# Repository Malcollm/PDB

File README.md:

# WiscoHumanoids Power Distribution Board

This repository contains the power distribution board (PDB) for the WiscoHumanoids humanoid robot. The board takes the 48 V battery, precharges the main bus, and distributes power to four high-current actuator branches. It also generates regulated 24 V, 6 V and 3.3 V rails for compute, hand servos, and sensors/control electronics.

**Status: Rev 1 has been fabricated and assembled by JLCPCB.**

## Rev 1 at a Glance

| | |
|---|---|
| Board size | 178.6 mm × 242.3 mm |
| Layers | 6 (FR-4 TG155, 1.6 mm) |
| Copper | 2 oz outer, 1 oz inner |
| Input | 48 V battery, 70 A BF1 main fuse |
| Current rating | 70 A for a few minutes; actuators expected to draw about 10 A RMS, 21 A peak (see [Current Ratings](#current-ratings)) |
| Outputs | 4 × 48 V actuator branches (XT30), 2 × 24 V, 1 × 6 V, 1 × 3.3 V |
| Current sensing | 7 × ACS758LCB-100B Hall-effect sensors (±100 A) |
| Assembly | 207 SMT/THT placements per board by JLCPCB (69 BOM lines); fuses and fuse holders installed by hand |

## Board Renders

| Isometric | Top |
|---|---|
|  |  |

## Copper Layers

Each layer is shown with the board outline and silkscreen so parts can be located on it.

| L1 (top) | L2 |
|---|---|
|  |  |
| Components, signal routing, 48 V power pours, PGND | Solid PGND plane |

| L3 | L4 |
|---|---|
|  |  |
| 48 V power pours (paralleling L1), PGND, some signal routing | Solid PGND plane |

| L5 | L6 (bottom) |
|---|---|
|  |  |
| PGND, signal routing | Signal routing, PGND |

The full schematic is in [`images/schematic.pdf`](images/schematic.pdf).

## System Power Architecture

```text
Battery + (J3)
   |
   F1  70 A main fuse (BF1)
   |
   +-- RPRE1 precharge resistor ---+
   +-- Precharge contactor --------+   (off-board, J13 -> J14)
                                   |
                       48V_PRECH: 6 x 470 uF bulk (2.82 mF)
                                   |
                       U4  main current sensor
                                   |
                               48V_MAIN
   +-------------------------------+-------------------------------+
   |                               |                               |
   F2                         3.3 V buck (U3)            E-stop contactor (off-board,
   24 V buck (U2)                  |                     JESTOP1 -> JESTOP2)
   U5  24 V current sensor         J4  3.3 V out                   |
   |                                                           48V_ESTOP -- Brake chopper / regen dump
   J5  24 V -> Jetson                                              |         (dump resistor on J16/J17)
   J6  24 V -> USB-C PD controller                                 U8  actuator group current sensor
                                                                   |
                                                                48V_ACT
                     +--------------+--------------+--------------+--------------+
                     |              |              |              |              |
                     F7             F6             F5             F4             F3
                     U10            U9             U12            U11            6 V buck (U7)
                     J8  ACT1       J7  ACT2       J10 ACT3       J9  ACT4       J12  6 V -> hand servos
```

Compute and control (24 V, 3.3 V) is fed from `48V_MAIN`, ahead of the E-stop contactor. It stays powered when the E-stop opens, so the robot can still monitor, communicate and shut down safely. Everything that moves (the four actuator branches and the 6 V hand-servo rail) is fed from `48V_ACT`, after the E-stop contactor.

## Power Rails

| Rail | Generated by | Connector(s) | Purpose |
|---|---|---|---|
| 48 V | Battery, through F1 and precharge | J8, J7, J10, J9 (XT30) | Actuator branches ACT1–ACT4, each individually fused and current-sensed |
| 24 V | LM5148 synchronous buck controller (U2), 10 µH | J5, J6 (Phoenix MC 3.81 mm) | Jetson compute and USB-C PD controller |
| 6 V | LM5148 synchronous buck controller (U7), 4.7 µH | J12 (Phoenix MC 3.81 mm) | Servo motors in the robot hands (E-stop protected) |
| 3.3 V | LMR36015 buck regulator (U3), 18 µH | J4 (Phoenix MC 3.81 mm) | Sensors, current sensors, regen comparator, control logic |

## Current Ratings

| | Current |
|---|---|
| Board rating | 70 A for a few minutes (exact duration to be confirmed by a Rev 1 load test) |
| Main fuse (F1) | 70 A Littelfuse BF1, 142.5631.5702 (58 V, M5 bolt-down) |
| Expected actuator draw | About 10 A RMS walking at 1.0 m/s; peaks of about 21 A (100 ms) and 28 A (10 ms) |

These are design targets. Rev 1 has not been load or thermally tested yet.

**Why the rating is far above the expected load:** the board is deliberately oversized. Rev 1's power path was laid out before we had current numbers for the robot. Those came later, from a walking simulation of the actuators. It counts the motors only, with no regen, and has about ±25% uncertainty. The worst case was walking at 1.0 m/s: about 10 A RMS at the battery, with peaks of about 21 A over 100 ms and 28 A over 10 ms. We still want the board rated well above that, with room for roughly twice the actuator current for future expansion. That headroom covers the actuators only; the compute and servo rails draw current on top of it.

Each output also has a limit set by its parts:

| Output | Limit | Set by |
|---|---|---|
| Each actuator output (ACT1–ACT4) | 15 A continuous, 30 A for 1 minute | XT30 connector |
| 24 V rail | About 8 A (190 W) | 24 V buck inductor (8.7 A rated) and 8 A per output connector |
| 6 V rail | 8 A (48 W) | J12 connector |
| 3.3 V rail | 1.5 A | LMR36015 regulator |

## Signal Connectors

The PDB has three low-voltage signal connectors, all JST-GH (1.25 mm pitch). They use 3.3 V logic and are referenced to PGND. In the tables below, **In** and **Out** are from the PDB's point of view.

| Connector | Pins | Purpose |
|---|---|---|
| J11 | 8 | Current-sense outputs |
| J2 | 4 | E-stop control and feedback |
| J24 | 6 | Precharge board interface |

The contactor coil and E-stop button terminals (J20, J21, J22) run at battery voltage, not logic level. They are covered under [Precharge Circuit](#precharge-circuit) and [E-Stop and Actuator Disconnect](#e-stop-and-actuator-disconnect).

### J11: Current Sense Outputs (JST-GH 8-pin)

| Pin | Net | Dir | Function |
|---|---|---|---|
| 1 | `Act_rail_curr` | Out | Actuator group current |
| 2 | (unnamed) | Out | ACT1 current |
| 3 | (unnamed) | Out | ACT2 current |
| 4 | (unnamed) | Out | ACT3 current |
| 5 | (unnamed) | Out | ACT4 current |
| 6 | `Main_curr` | Out | Main battery current |
| 7 | `Com_cur` | Out | 24 V rail current |
| 8 | GND | | PGND |

To convert the readings to amps, see [Analog Conversions](#analog-conversions).

### J2: E-Stop Logic (JST-GH 4-pin)

| Pin | Net | Dir | Function |
|---|---|---|---|
| 1 | GND | | PGND |
| 2 | `ESTOP_FB` | Out | Low when the E-stop contactor coil is on |
| 3 | `ESTOP_EN2` | In | E-stop contactor enable 2 |
| 4 | `ESTOP_EN1` | In | E-stop contactor enable 1 |

The actuators are powered only when both enables are high and the E-stop button is closed. The enables are pulled down, so an unplugged connector keeps the actuators off.

### J24: Precharge Board Interface (JST-GH 6-pin)

| Pin | Net | Dir | Function |
|---|---|---|---|
| 1 | GND | | PGND |
| 2 | +3.3V | Out | 3.3 V supply for the precharge board |
| 3 | `PRECH_EN` | In | Closes the precharge contactor |
| 4 | `24V_EN_IN` | In | Turns on the 24 V rail |
| 5 | `PRECH_SENSE` | Out | Bus voltage ÷ 26.6 |
| 6 | `BATT_SENSE` | Out | Battery voltage ÷ 26.6 |

Both enables are active high and default to off. The precharge board compares the bus and battery voltages, then closes the contactor once the bus has charged. The 24 V rail stays off until it is enabled, which keeps the Jetson's load off the precharge resistor.

### Analog Conversions

To log the analog outputs, convert the voltage measured at the pin (`V`) as follows:

| Signal | Pins | Conversion | Range |
|---|---|---|---|
| Current sense | J11 pins 1–7 | `I (A) = (V − 1.65) / 0.0132` | ±100 A spans 0.33–2.97 V; 0 A reads 1.65 V |
| `PRECH_SENSE`, `BATT_SENSE` | J24 pins 5–6 | `Voltage (V) = V × 26.64` | 48 V reads 1.80 V; 3.3 V at the pin is 87.9 V |

- Positive current flows toward the load. Negative current is regen flowing back toward the battery.
- The current-sense outputs scale with the PDB's 3.3 V rail. If the logger's ADC uses a different reference, multiply 1.65 and 0.0132 by (measured 3.3 V rail ÷ 3.3).

## Major Board Features

### 48 V Actuator Distribution

The main power path distributes 48 V battery power to four actuator branches. Each branch has its own 20 A ATO blade fuse (F4–F7), current sensor and TVS diode, and leaves the board on an XT30 connector. Because this path carries the highest current on the board, the 48 V nets are poured on both L1 and L3, with short current paths and bolt-down M5 connections for the battery and contactors.

### Precharge Circuit

The main bus carries 2.82 mF of bulk capacitance, so connecting the battery directly would cause a large inrush current. The precharge resistor RPRE1 sits permanently across an off-board precharge contactor (J13/J14), so the bus charges slowly through RPRE1 when the battery is connected. An external controller watches the battery and bus voltages, then closes the contactor (through an MCP1402 gate driver and Q1) to bypass the resistor.

The precharge board connects on **J24** (pinout in [Signal Connectors](#j24-precharge-board-interface-jst-gh-6-pin)). The contactor coil connects to **J22**.

### E-Stop and Actuator Disconnect

An off-board E-stop contactor between JESTOP1 and JESTOP2 separates the actuator/servo group from the compute/control group. Its coil (**J20**) is powered through the normally-closed E-stop button (**J21**) and two series FETs (Q2/Q3), driven by MCP1402 gate drivers. The two enables and a feedback line are on **J2** (pinout in [Signal Connectors](#j2-e-stop-logic-jst-gh-4-pin)). Opening either the button or an enable drops the actuator group while compute stays up.

### Regen Protection (Brake Chopper)

When actuators decelerate they push energy back into the bus. If the battery can't take it (E-stop open, BMS charge FET open, or a full pack), the bus voltage rises. A TLV3011 comparator (U1) watches the actuator bus. When it crosses its trip point, a UCC27511 gate driver (U6) switches Q6/Q9 to dump the excess into an external 1 Ω, 200 W chassis-mount resistor on **J16/J17**. Pulling jumper **J18** (`BC_Disconnect`) disables the chopper.

### Current Sensing

Seven ACS758LCB-100B bidirectional Hall-effect sensors monitor:

| Sensor | Path |
|---|---|
| U4 | Main battery input (after precharge) |
| U8 | Actuator group, after the E-stop contactor |
| U10, U9, U12, U11 | Actuator branches ACT1–ACT4 |
| U5 | 24 V rail output |

Each output is RC-filtered and brought out on **J11** for the robot's controller (pinout in [J11](#j11-current-sense-outputs-jst-gh-8-pin), scaling in [Analog Conversions](#analog-conversions)). Current measurement is used for detecting abnormal loads, debugging actuator behavior, estimating power use, and measuring regen.

### Protection

- 70 A main fuse (F1, Littelfuse BF1 142.5631.5702, M5 bolt-down)
- 20 A ATO blade fuses on each actuator branch (F4–F7), a 10 A fuse on the 24 V compute buck input (F2) and a 5 A fuse on the 6 V servo buck input (F3)
- 0.5 A fuses on the contactor coil supplies (F8, F10)
- SMC TVS diodes on the fused 48 V input, each actuator branch, and the 24 V and 6 V outputs
- Varistor across the E-stop contactor coil; flyback diode on the precharge contactor coil
- Precharge / inrush-current limiting
- Brake-chopper regen dump
- Separation between actuator/servo power and compute/control power

### Test Points

TP1–TP16 and TP20 are Keystone 5015 test points on PGND, the E-stop, precharge and regen-dump control signals, and the converter bias rails. TP17–TP19 are bare probe pads on the switch nodes of the 24 V, 6 V and 3.3 V converters.

### Off-Board Parts (Rev 1)

Rev 1 has these parts mounted off the board, bolted to its M5 pads:

| Part | Connects to | Rev 2 plan |
|---|---|---|
| Precharge contactor | J13 / J14 (coil on J22) | Replace with power FETs on the board |
| E-stop contactor | JESTOP1 / JESTOP2 (coil on J20) | Replace with power FETs on the board |
| 1 Ω, 200 W chassis-mount dump resistor | J16 / J17 | Find a smaller solution |
| Dump resistor freewheel diode (DFB2) | Across the dump resistor: cathode to J16, anode to J17 | Move onto the board |

## Grounding

The board uses one power ground plus local analog grounds:

| Net | Purpose |
|---|---|
| PGND | High-current power ground and switching converter return. Continuous reference planes on L2 and L4; on L1, L3, L5 and L6 it is poured around signal routing |
| AGND, AGND1–AGND10 | Local analog grounds for each buck converter's feedback network, each current sensor, and the regen comparator |

Each local AGND joins PGND at one point through a net tie (NT1–NT11). This keeps large return currents out of the feedback and measurement references.

## Simulations

LTspice simulations live in [`LTspice Simulations/`](LTspice%20Simulations/). Each folder has a `.lib` of behavioral models and the matching `.asy` symbols the schematics use.

| Simulation | Purpose |
|---|---|
| `precharge/precharge_resistor_sweep.asc` | Sweeps the precharge resistor value (the board uses 100 Ω) to compare bus charge time against resistor and main-fuse stress |
| `precharge/precharge_load_sweep.asc` | With the board's 100 Ω resistor, sweeps the load drawn during precharge to check the bus still reaches full voltage before the contactor closes |
| `regen/regen_earlier_design.asc` | An earlier version of the regen dump circuit, kept for reference. It is expected to fail its checks; the sim below shows the fixes |
| `regen/regen_current_sweep.asc` | The regen dump circuit with the fixes (freewheel diode, local ceramic, sense filter, gate pulldown), the board's resistor values and TVS diodes, and the 1 Ω dump resistor. Sweeps regen current from 10 to 50 A, held for 10 ms; 28 A is the worst 10 ms battery peak from the walking simulation. Checks the actuators stay under their 55 V maximum, the dump FET under 80 V, and the TVS diodes don't conduct |

Results are written to the SPICE output log as `.meas` values, including pass/fail checks.

## Repository Layout

| Path | Contents |
|---|---|
| `Main_PDB.kicad_pro` / `.kicad_sch` / `.kicad_pcb` | KiCad 10 project, schematic and board |
| `Main_PDB.kicad_dru` | Custom design rules (JLCPCB 6-layer, 2 oz outer copper limits, net-tie exceptions) |
| `Footprints.pretty/`, `Symbols/`, `3d Models/` | Project libraries and 3D models |
| `production/` | Rev 1 manufacturing outputs: gerbers (`PDB_PCB.zip`), BOM, pick-and-place, IPC netlist |
| `images/` | Board renders, layer SVGs and schematic PDF, regenerated from the design files (see [`images/regenerate-images.md`](images/regenerate-images.md)) |
| `LTspice Simulations/` | Precharge and regen protection simulations |

The images are rebuilt by a pre-commit hook whenever the board or schematic changes. Enable it once per clone with `git config core.hooksPath images/hooks`.

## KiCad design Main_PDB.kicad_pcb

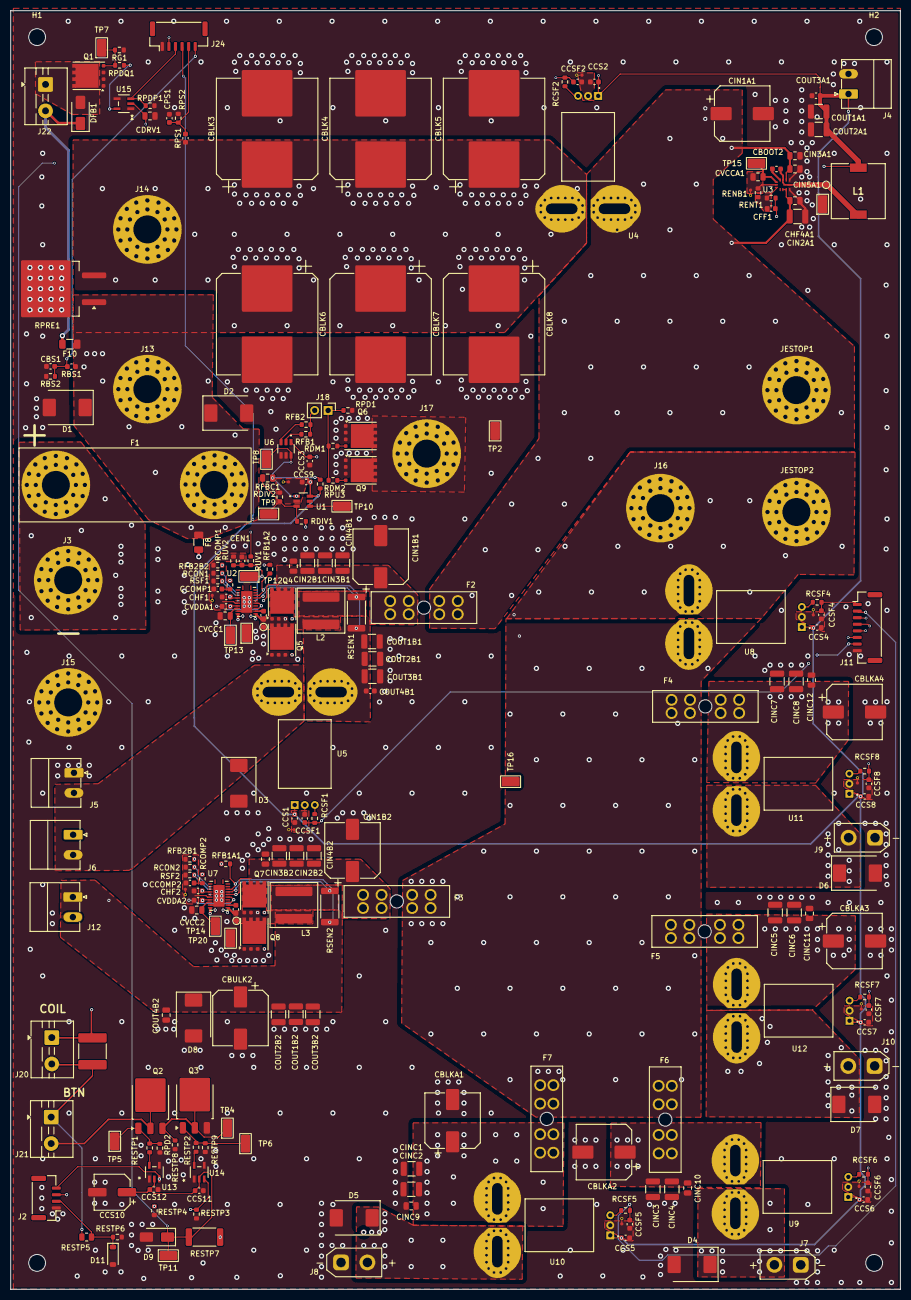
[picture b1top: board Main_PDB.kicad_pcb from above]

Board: 6 copper layers, 168.6 x 242.3 mm, 241 parts (0 on the bottom side), 105 nets.

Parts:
CBLK3, CBLK4, CBLK5, CBLK6, CBLK7, CBLK8: 470uF; CP_Elec_18x22
CBLKA1, CBLKA2: 100uF; CP_Elec_10x10
CBLKA3, CBLKA4: 47uF; CP_Elec_10x10
CBOOT1, CBOOT2, CBOOT3: 100nF; C_0603_1608Metric
CBS1: 100nF; C_0603_1608Metric
CBULK2: 100uF; CP_Elec_10x10
CCOMP1: 2nF; C_0603_1608Metric
CCOMP2: 2.7nF; C_0603_1608Metric
CCS1, CCS2, CCS3, CCS4, CCS5, CCS6, CCS7, CCS8, CCS9, CCS11, CCS12: 100nF; C_0603_1608Metric
CCS10: 100uF; CP_Elec_6.3x5.4
CCSF1, CCSF2, CCSF4, CCSF5, CCSF6, CCSF7, CCSF8: 10nF; C_0603_1608Metric
CDRV1: 1uF; C_0805_2012Metric
CEN1: 1nF; C_0603_1608Metric
CFF1: 22pF; C_0603_1608Metric
CHF1, CHF2: 22pF; C_0603_1608Metric
CHF4A1: 220nF; C_0805_2012Metric
CIN1A1, CIN1B1: 47uF; CP_Elec_10x10
CIN1B2: 100uF; CP_Elec_10x10
CIN2A1, CIN2B1, CIN2B2, CIN3B1, CIN3B2, CIN4B1, CIN4B2: 4.7uF; C_1210_3225Metric
CIN3A1: 220nF; C_0805_2012Metric
CIN5A1, CIN5B1, CIN5B2: 100nF; C_0805_2012Metric
CINC1, CINC2, CINC3, CINC4, CINC5, CINC6, CINC7, CINC8: 4.7uF; C_1210_3225Metric
CINC9, CINC10, CINC11, CINC12: 100nF; C_0805_2012Metric
COUT1A1, COUT2A1: 47uF; C_1210_3225Metric
COUT1B1, COUT1B2, COUT2B1, COUT2B2, COUT3B1, COUT3B2: 22uF; C_1210_3225Metric
COUT3A1, COUT4B1: 100nF; C_0603_1608Metric
COUT4B2: 100nF; C_0805_2012Metric
CPS1: 100nF; C_0603_1608Metric
CVCC1, CVCC2: 2.2uF; C_0805_2012Metric
CVCCA1: 1uF; C_0805_2012Metric
CVDDA1, CVDDA2: 100nF; C_0603_1608Metric
D1, D2, D4, D5, D6, D7: SMCJ58A; D_SMC
D3: SMCJ26A; D_SMC
D8: SMCJ6.5A; D_SMC
D9: SMAZ12-13-F; D_SMA
D11: MMSZ5226BT1G; D_SOD-123
DFB1: S1M-13-F; D_SMA
F1: 70A; FUSE_BF1_M5
F2, F3, F4, F5, F6, F7: 178.6165.0002; LITTELFUSE_178.6165.0002
F8, F10: 0.5A; Fuse_1206_3216Metric
H1, H2, H3, H4: MountingHole_3.2mm_M3
J2: E-stop Ctrl; JST_GH_BM04B-GHS-TBT_1x04-1MP_P1.25mm_Vertical
J3: Conn_Batt_PWR; MountingHole_5.3mm_M5_Pad_Via_HP
J4: 3.3V Out; PhoenixContact_MC_1,5_2-G-3.81_1x02_P3.81mm_Horizontal
J5: 24V Out -> Jetson; PhoenixContact_MC_1,5_2-G-3.81_1x02_P3.81mm_Horizontal
J6: 24V Out -> USB-C-PD controller; PhoenixContact_MC_1,5_2-G-3.81_1x02_P3.81mm_Horizontal
J7: ACT2 Out; AMASS_XT30UPB-F_1x02_P5.0mm_Vertical
J8: ACT1 Out; AMASS_XT30UPB-F_1x02_P5.0mm_Vertical
J9: ACT4 Out; AMASS_XT30UPB-F_1x02_P5.0mm_Vertical
J10: ACT3 Out; AMASS_XT30UPB-F_1x02_P5.0mm_Vertical
J11: Current Sense Out; JST_GH_BM08B-GHS-TBT_1x08-1MP_P1.25mm_Vertical
J12: 6V Out; PhoenixContact_MC_1,5_2-G-3.81_1x02_P3.81mm_Horizontal
J13: PRECIN; MountingHole_5.3mm_M5_Pad_Via_HP
J14: PRECOUT; MountingHole_5.3mm_M5_Pad_Via_HP
J15: Conn_Batt_GND; MountingHole_5.3mm_M5_Pad_Via_HP
J16: Dump_Resistor_In; MountingHole_5.3mm_M5_Pad_Via_HP
J17: Dump_Resistor_Out; MountingHole_5.3mm_M5_Pad_Via_HP
J18: BC_Disconnect; PinHeader_1x02_P2.54mm_Vertical
J20: ESTOP Contactor Coil Control; TerminalBlock_MaiXu_MX126-5.0-02P_1x02_P5.00mm
J21: ESTOP Button (Normally Closed); TerminalBlock_MaiXu_MX126-5.0-02P_1x02_P5.00mm
J22: Precharge Contactor Coil Control; TerminalBlock_MaiXu_MX126-5.0-02P_1x02_P5.00mm
J24: Precharge Ctrl In; JST_GH_BM06B-GHS-TBT_1x06-1MP_P1.25mm_Vertical
JESTOP1: ESTOP_IN; MountingHole_5.3mm_M5_Pad_Via_HP
JESTOP2: ESTOP_OUT; MountingHole_5.3mm_M5_Pad_Via_HP
L1: 18uH; L_Sumida_CDRH104R
L2: 10uH; L_Coilank_AAPS0880
L3: 4.7uH; L_Coilcraft_XAL8080-XXX
NT1, NT2, NT3, NT4, NT5, NT6, NT7, NT8, NT9, NT10, NT11: NetTie_2; NetTie_AGND_PGND_VIA
Q1, Q5, Q6, Q8, Q9: BSC070N10LS5ATMA1; VSONP-8-1EP_5x6_P1.27mm
Q2, Q3: IRFR220TRPBF; TO-252-3_TabPin2
Q4, Q7: BSC146N10LS5; VSONP-8-1EP_5x6_P1.27mm
RBS1: 100k; C_0603_1608Metric
RBS2: 3.9k; R_0603_1608Metric
RCOMP1: 19.1k; R_0603_1608Metric
RCOMP2: 12.1k; R_0603_1608Metric
RCON1, RCON2: 41.2k; R_0603_1608Metric
RCSF1, RCSF2, RCSF4, RCSF5, RCSF6, RCSF7, RCSF8: 1k; R_0603_1608Metric
RDIV1: 1M; R_0603_1608Metric
RDIV2: 24k; R_0603_1608Metric
RDM1, RDM2: 2.2R; R_0603_1608Metric
RENB1: 43.2k; R_0603_1608Metric
RENT1: 100k; R_0603_1608Metric
RESTP1, RESTP2: 100R; R_0603_1608Metric
RESTP3, RESTP4: 2.2k; R_0603_1608Metric
RESTP5: 100k; R_0805_2012Metric
RESTP6: 7.5k; R_0603_1608Metric
RESTP7: 4.7k; R_2512_6332Metric
RESTP8, RESTP9: 100k; R_0603_1608Metric
RFB1, RFB2: 4.7R; R_0603_1608Metric
RFB1A1: 64.9k; R_0603_1608Metric
RFB1A2: 291k; R_0603_1608Metric
RFB2B1, RFB2B2: 10k; R_0603_1608Metric
RFBC1: 1.6M; C_0805_2012Metric
RG1: 100R; R_0603_1608Metric
RPD1, RPD2: 100k; R_0603_1608Metric
RPDP1: 100k; R_0603_1608Metric
RPDQ1: 100k; R_0603_1608Metric
RPRE1: 100; TO-263-2_Resistor
RPS1: 100k; C_0603_1608Metric
RPS2: 3.9k; R_0603_1608Metric
RPU3: 10k; R_0603_1608Metric
RSEN1, RSEN2: 0.004R; R_2512_6332Metric
RSF1, RSF2: 47k; R_0603_1608Metric
RUV1, RUV2: 100k; R_0603_1608Metric
RV1: RL2220A820K-452A; C_2220_5750Metric
TP1, TP2, TP3, TP4, TP5, TP6, TP7, TP8, TP9, TP10, TP11, TP12, TP13, TP14, TP15, TP16: Keystone 5015; TestPoint_Keystone_5015_Micro_Mini
TP17, TP18, TP19: SW probe pad; TestPoint_Pad_D1.0mm
TP20: PGND probe pad; TestPoint_Keystone_5015_Micro_Mini
U1: TLV3011AIDBVT; SOT95P280X145-6N
U2, U7: LM5148RGYR; QFN50P550X350X100-25N
U3: LMR36015ARNXR; RNX0012B
U4, U5, U8, U9, U10, U11, U12: ACS758LCB-100B-PFF-T; XDCR_ACS758LCB-100B-PFF-T
U6: UCC27511DBVR; SOT95P280X145-6N
U13, U14, U15: MCP1402T-E/OT; SOT-23-5_MC_MCH

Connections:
+3.3V: CCS1.1, CCS2.2, CCS4.2, CCS5.1, CCS6.1, CCS7.1, CCS8.1, CCS9.1, CFF1.1, COUT1A1.1, COUT2A1.1, COUT3A1.1, J4.1, J24.2, L1.2, RENT1.1, RPU3.2, U1.6 (V+), U4.1 (VCC), U5.1 (VCC), U8.1 (VCC), U9.1 (VCC), U10.1 (VCC), U11.1 (VCC), U12.1 (VCC)
+6V: CBULK2.1, CCS3.1, COUT1B2.1, COUT2B2.1, COUT3B2.1, COUT4B2.1, D8.1 (K), J12.1, RFB1A1.2, RSEN2.2, U6.1 (VDD), U7.21 (VOUT)
+6V_IND: L3.2, RSEN2.1, U7.20 (ISNS+)
+24V: D3.1 (K), J5.2, J6.2, U5.5 (IP-), U5.5_1 (IP-), U5.5_2 (IP-), U5.5_3 (IP-), U5.5_4 (IP-), U5.5_5 (IP-), U5.5_6 (IP-), U5.5_7 (IP-), U5.5_8 (IP-), U5.5_9 (IP-), U5.5_10 (IP-), U5.5_11 (IP-), U5.5_12 (IP-), U5.5_13 (IP-), U5.5_14 (IP-), U5.5_15 (IP-), U5.5_16 (IP-)
+48V_BATT: F1.1, J3.1 (Pin_1_1)
/3V3_SW: CBOOT2.2, L1.1, TP19.1 (1_1), U3.3 (NC), U3.12 (SW)
/3V3_VCC: CVCCA1.2, TP15.1 (1_1), U3.5 (VCC)
/6V_FUSE: CIN1B2.1, CIN2B2.2, CIN3B2.2, CIN4B2.2, CIN5B2.2, F3.2_1, F3.2_2, F3.2_3, F3.2_4, Q7.3 (D), U7.12 (VIN), U7.19 (EN)
/6V_NMOS: CBOOT3.1, L3.1, Q7.1 (S), Q8.3 (D), TP18.1 (1_1), U7.14 (SW)
/6V_VCC: CVCC2.1, TP14.1 (1_1), U7.9 (VCC)
/12V_BIAS: CCS10.1, CCS11.2, CCS12.2, CDRV1.1, D9.1 (K), RESTP7.2, TP11.1 (1_1), U13.2 (VDD), U14.2 (VDD), U15.2 (VDD)
/24V_EN: CEN1.1, RUV1.2, RUV2.1, TP12.1 (1_1), U2.19 (EN)
/24V_EN_IN: J24.4, RUV1.1
/24V_FUSE: CIN1B1.1, CIN2B1.2, CIN3B1.2, CIN4B1.2, CIN5B1.2, F2.2_1, F2.2_2, F2.2_3, F2.2_4, Q4.3 (D), U2.12 (VIN)
/24V_IND: L2.2, RSEN1.1, U2.20 (ISNS+)
/24V_NMOS: CBOOT1.2, L2.1, Q4.1 (S), Q5.3 (D), TP17.1 (1_1), U2.14 (SW)
/24V_SEN: COUT1B1.1, COUT2B1.1, COUT3B1.1, COUT4B1.1, RFB1A2.2, RSEN1.2, U2.21 (VOUT), U5.4 (IP+), U5.4_1 (IP+), U5.4_2 (IP+), U5.4_3 (IP+), U5.4_4 (IP+), U5.4_5 (IP+), U5.4_6 (IP+), U5.4_7 (IP+), U5.4_8 (IP+), U5.4_9 (IP+), U5.4_10 (IP+), U5.4_11 (IP+), U5.4_12 (IP+), U5.4_13 (IP+), U5.4_14 (IP+), U5.4_15 (IP+), U5.4_16 (IP+)
/24V_VCC: CVCC1.1, TP13.1 (1_1), U2.9 (VCC)
/48V_ACT: F3.1_1, F3.1_2, F3.1_3, F3.1_4, F4.1_1, F4.1_2, F4.1_3, F4.1_4, F5.1_1, F5.1_2, F5.1_3, F5.1_4, F6.1_1, F6.1_2, F6.1_3, F6.1_4, F7.1_1, F7.1_2, F7.1_3, F7.1_4, U8.5 (IP-), U8.5_1 (IP-), U8.5_2 (IP-), U8.5_3 (IP-), U8.5_4 (IP-), U8.5_5 (IP-), U8.5_6 (IP-), U8.5_7 (IP-), U8.5_8 (IP-), U8.5_9 (IP-), U8.5_10 (IP-), U8.5_11 (IP-), U8.5_12 (IP-), U8.5_13 (IP-), U8.5_14 (IP-), U8.5_15 (IP-), U8.5_16 (IP-)
/48V_ACT1: D5.1 (K), J8.2, U10.5 (IP-), U10.5_1 (IP-), U10.5_2 (IP-), U10.5_3 (IP-), U10.5_4 (IP-), U10.5_5 (IP-), U10.5_6 (IP-), U10.5_7 (IP-), U10.5_8 (IP-), U10.5_9 (IP-), U10.5_10 (IP-), U10.5_11 (IP-), U10.5_12 (IP-), U10.5_13 (IP-), U10.5_14 (IP-), U10.5_15 (IP-), U10.5_16 (IP-)
/48V_ACT1_FUSE: CBLKA1.1, CINC1.2, CINC2.2, CINC9.1, F7.2_1, F7.2_2, F7.2_3, F7.2_4, U10.4 (IP+), U10.4_1 (IP+), U10.4_2 (IP+), U10.4_3 (IP+), U10.4_4 (IP+), U10.4_5 (IP+), U10.4_6 (IP+), U10.4_7 (IP+), U10.4_8 (IP+), U10.4_9 (IP+), U10.4_10 (IP+), U10.4_11 (IP+), U10.4_12 (IP+), U10.4_13 (IP+), U10.4_14 (IP+), U10.4_15 (IP+), U10.4_16 (IP+)
/48V_ACT2: D4.1 (K), J7.2, U9.5 (IP-), U9.5_1 (IP-), U9.5_2 (IP-), U9.5_3 (IP-), U9.5_4 (IP-), U9.5_5 (IP-), U9.5_6 (IP-), U9.5_7 (IP-), U9.5_8 (IP-), U9.5_9 (IP-), U9.5_10 (IP-), U9.5_11 (IP-), U9.5_12 (IP-), U9.5_13 (IP-), U9.5_14 (IP-), U9.5_15 (IP-), U9.5_16 (IP-)
/48V_ACT2_FUSE: CBLKA2.1, CINC3.2, CINC4.2, CINC10.1, F6.2_1, F6.2_2, F6.2_3, F6.2_4, U9.4 (IP+), U9.4_1 (IP+), U9.4_2 (IP+), U9.4_3 (IP+), U9.4_4 (IP+), U9.4_5 (IP+), U9.4_6 (IP+), U9.4_7 (IP+), U9.4_8 (IP+), U9.4_9 (IP+), U9.4_10 (IP+), U9.4_11 (IP+), U9.4_12 (IP+), U9.4_13 (IP+), U9.4_14 (IP+), U9.4_15 (IP+), U9.4_16 (IP+)
/48V_ACT3: D7.1 (K), J10.2, U12.5 (IP-), U12.5_1 (IP-), U12.5_2 (IP-), U12.5_3 (IP-), U12.5_4 (IP-), U12.5_5 (IP-), U12.5_6 (IP-), U12.5_7 (IP-), U12.5_8 (IP-), U12.5_9 (IP-), U12.5_10 (IP-), U12.5_11 (IP-), U12.5_12 (IP-), U12.5_13 (IP-), U12.5_14 (IP-), U12.5_15 (IP-), U12.5_16 (IP-)
/48V_ACT3_FUSE: CBLKA3.1, CINC5.2, CINC6.2, CINC11.1, F5.2_1, F5.2_2, F5.2_3, F5.2_4, U12.4 (IP+), U12.4_1 (IP+), U12.4_2 (IP+), U12.4_3 (IP+), U12.4_4 (IP+), U12.4_5 (IP+), U12.4_6 (IP+), U12.4_7 (IP+), U12.4_8 (IP+), U12.4_9 (IP+), U12.4_10 (IP+), U12.4_11 (IP+), U12.4_12 (IP+), U12.4_13 (IP+), U12.4_14 (IP+), U12.4_15 (IP+), U12.4_16 (IP+)
/48V_ACT4: D6.1 (K), J9.2, U11.5 (IP-), U11.5_1 (IP-), U11.5_2 (IP-), U11.5_3 (IP-), U11.5_4 (IP-), U11.5_5 (IP-), U11.5_6 (IP-), U11.5_7 (IP-), U11.5_8 (IP-), U11.5_9 (IP-), U11.5_10 (IP-), U11.5_11 (IP-), U11.5_12 (IP-), U11.5_13 (IP-), U11.5_14 (IP-), U11.5_15 (IP-), U11.5_16 (IP-)
/48V_ACT4_FUSE: CBLKA4.1, CINC7.2, CINC8.2, CINC12.1, F4.2_1, F4.2_2, F4.2_3, F4.2_4, U11.4 (IP+), U11.4_1 (IP+), U11.4_2 (IP+), U11.4_3 (IP+), U11.4_4 (IP+), U11.4_5 (IP+), U11.4_6 (IP+), U11.4_7 (IP+), U11.4_8 (IP+), U11.4_9 (IP+), U11.4_10 (IP+), U11.4_11 (IP+), U11.4_12 (IP+), U11.4_13 (IP+), U11.4_14 (IP+), U11.4_15 (IP+), U11.4_16 (IP+)
/48V_ESTOP: J16.1 (Pin_1_1), JESTOP2.1 (Pin_1_1), RDIV1.1, U8.4 (IP+), U8.4_1 (IP+), U8.4_2 (IP+), U8.4_3 (IP+), U8.4_4 (IP+), U8.4_5 (IP+), U8.4_6 (IP+), U8.4_7 (IP+), U8.4_8 (IP+), U8.4_9 (IP+), U8.4_10 (IP+), U8.4_11 (IP+), U8.4_12 (IP+), U8.4_13 (IP+), U8.4_14 (IP+), U8.4_15 (IP+), U8.4_16 (IP+)
/48V_FUSE: D1.1 (K), D2.1 (K), F1.2, F8.1, F10.1, J13.1 (Pin_1_1), RBS1.1, RPRE1.1
/48V_MAIN: CHF4A1.1, CIN1A1.1, CIN2A1.1, CIN3A1.1, CIN5A1.1, F2.1_1, F2.1_2, F2.1_3, F2.1_4, JESTOP1.1 (Pin_1_1), U3.2 (VIN), U3.9 (EN), U3.10 (VIN), U4.5 (IP-), U4.5_1 (IP-), U4.5_2 (IP-), U4.5_3 (IP-), U4.5_4 (IP-), U4.5_5 (IP-), U4.5_6 (IP-), U4.5_7 (IP-), U4.5_8 (IP-), U4.5_9 (IP-), U4.5_10 (IP-), U4.5_11 (IP-), U4.5_12 (IP-), U4.5_13 (IP-), U4.5_14 (IP-), U4.5_15 (IP-), U4.5_16 (IP-)
/48V_PRECH: CBLK3.1, CBLK4.1, CBLK5.1, CBLK6.1, CBLK7.1, CBLK8.1, J14.1 (Pin_1_1), RPRE1.2, RPS1.1, U4.4 (IP+), U4.4_1 (IP+), U4.4_2 (IP+), U4.4_3 (IP+), U4.4_4 (IP+), U4.4_5 (IP+), U4.4_6 (IP+), U4.4_7 (IP+), U4.4_8 (IP+), U4.4_9 (IP+), U4.4_10 (IP+), U4.4_11 (IP+), U4.4_12 (IP+), U4.4_13 (IP+), U4.4_14 (IP+), U4.4_15 (IP+), U4.4_16 (IP+)
/Act_rail_curr: CCSF4.2, J11.1, RCSF4.2
/BATT_SENSE: CBS1.1, J24.6, RBS1.2, RBS2.1
/Com_cur: CCSF1.2, J11.7, RCSF1.2
/DUMP_REF: TP10.1 (1_1), U1.4 (IN-), U1.5 (REF)
/DUMP_SENSE: RDIV1.2, RDIV2.1, RFBC1.2, TP9.1 (1_1), U1.3 (IN+)
/DUMP_TRIG: RFBC1.1, RPU3.1, TP8.1 (1_1), U1.1 (OUT), U6.6 (IN+)
/D_R_OUT: J17.1 (Pin_1_1), Q6.3 (D), Q9.3 (D)
/ESTOP_EN1: J2.4, RESTP4.2, U13.3 (IN)
/ESTOP_EN2: J2.3, RESTP3.1, U14.3 (IN)
/ESTOP_FB: D11.1 (K), J2.2, RESTP5.2, RESTP6.1
/ESTOP_FET_MID: Q2.3 (S), Q3.2 (D), RPD2.2, TP4.1 (1_1)
/ESTOP_G1: Q2.1 (G), RESTP1.1, RESTP8.1, TP5.1 (1_1)
/ESTOP_G2: Q3.1 (G), RESTP2.1, RESTP9.2, TP6.1 (1_1)
/Main_curr: CCSF2.2, J11.6, RCSF2.2
/PRECH_EN: J24.3, RPDP1.1, U15.3 (IN)
/PRECH_GATE: Q1.2 (G), RG1.1, RPDQ1.1, TP7.1 (1_1)
/PRECH_SENSE: CPS1.1, J24.5, RPS1.2, RPS2.1
AGND: CCS2.1, CCSF2.1, NT10.1, U4.2 (GND)
AGND1: CCS9.2, NT1.1, RDIV2.2, U1.2 (V-)
AGND2: CCOMP1.2, CEN1.2, CHF1.2, CVDDA1.1, NT2.1, RCON1.1, RFB2B2.1, RSF1.1, RUV2.2, U2.7 (AGND), U2.16 (VCCX), U2.18 (PFM/SYNC)
AGND3: CCOMP2.2, CHF2.2, CVDDA2.1, NT3.1, RCON2.1, RFB2B1.1, RSF2.1, U7.7 (AGND), U7.16 (VCCX), U7.18 (PFM/SYNC)
AGND4: CCS1.2, CCSF1.1, NT4.1, U5.2 (GND)
AGND5: CVCCA1.1, NT5.1, RENB1.2, U3.6 (AGND)
AGND6: CCS4.1, CCSF4.1, NT6.1, U8.2 (GND)
AGND7: CCS5.2, CCSF5.1, NT7.1, U10.2 (GND)
AGND8: CCS6.2, CCSF6.1, NT8.1, U9.2 (GND)
AGND9: CCS7.2, CCSF7.1, NT9.1, U12.2 (GND)
AGND10: CCS8.2, CCSF8.1, NT11.1, U11.2 (GND)
unnamed: CCOMP1.1, RCOMP1.2
unnamed: CCOMP2.1, RCOMP2.2
unnamed: DFB1.2 (A), J22.1, Q1.3 (D)
unnamed: DFB1.1 (K), F10.2, J22.2
unnamed: CCSF5.2, J11.2, RCSF5.2
unnamed: CCSF6.2, J11.3, RCSF6.2
unnamed: CCSF7.2, J11.4, RCSF7.2
unnamed: CCSF8.2, J11.5, RCSF8.2
unnamed: J18.1, RDM1.2, RDM2.2, RPD1.2
unnamed: J18.2, RFB1.2, RFB2.2
unnamed: F8.2, J20.1, RESTP7.1, RV1.2
unnamed: J20.2, J21.1, RESTP5.1, RV1.1
unnamed: J21.2, Q2.2 (D)
unnamed: Q4.2 (G), U2.13 (HO)
unnamed: Q5.2 (G), U2.11 (LO)
unnamed: Q6.2 (G), RDM1.1
unnamed: Q7.2 (G), U7.13 (HO)
unnamed: Q8.2 (G), U7.11 (LO)
unnamed: Q9.2 (G), RDM2.1
unnamed: CBOOT1.1, U2.15 (CBOOT)
unnamed: RCON1.2, U2.3 (CNFG)
unnamed: CHF1.1, RCOMP1.1, U2.5 (EXTCOMP)
unnamed: RFB1A2.1, RFB2B2.2, U2.6 (FB)
unnamed: RSF1.2, U2.4 (RT)
unnamed: CVDDA1.2, U2.8 (VDDA)
unnamed: CBOOT2.1, U3.4 (BST)
unnamed: CFF1.2, RENB1.1, RENT1.2, U3.7 (FB)
unnamed: RCSF2.1, U4.3 (VIOUT)
unnamed: RCSF1.1, U5.3 (VIOUT)
unnamed: RFB1.1, U6.2 (OUTH)
unnamed: RFB2.1, U6.3 (OUTL)
unnamed: CBOOT3.2, U7.15 (CBOOT)
unnamed: RCON2.2, U7.3 (CNFG)
unnamed: CHF2.1, RCOMP2.1, U7.5 (EXTCOMP)
unnamed: RFB1A1.1, RFB2B1.2, U7.6 (FB)
unnamed: RSF2.2, U7.4 (RT)
unnamed: CVDDA2.2, U7.8 (VDDA)
unnamed: RCSF4.1, U8.3 (VIOUT)
unnamed: RCSF6.1, U9.3 (VIOUT)
unnamed: RCSF5.1, U10.3 (VIOUT)
unnamed: RCSF8.1, U11.3 (VIOUT)
unnamed: RCSF7.1, U12.3 (VIOUT)
unnamed: RESTP1.2, U13.5 (OUT)
unnamed: RESTP2.2, U14.5 (OUT)
unnamed: RG1.2, U15.5 (OUT)
PGND: CBLK3.2, CBLK4.2, CBLK5.2, CBLK6.2, CBLK7.2, CBLK8.2, CBLKA1.2, CBLKA2.2, CBLKA3.2, CBLKA4.2, CBS1.2, CBULK2.2, CCS3.2, CCS10.2, CCS11.1, CCS12.1, CDRV1.2, CHF4A1.2, CIN1A1.2, CIN1B1.2, CIN1B2.2, CIN2A1.2, CIN2B1.1, CIN2B2.1, CIN3A1.2, CIN3B1.1, CIN3B2.1, CIN4B1.1, CIN4B2.1, CIN5A1.2, CIN5B1.1, CIN5B2.1, CINC1.1, CINC2.1, CINC3.1, CINC4.1, CINC5.1, CINC6.1, CINC7.1, CINC8.1, CINC9.2, CINC10.2, CINC11.2, CINC12.2, COUT1A1.2, COUT1B1.2, COUT1B2.2, COUT2A1.2, COUT2B1.2, COUT2B2.2, COUT3A1.2, COUT3B1.2, COUT3B2.2, COUT4B1.2, COUT4B2.2, CPS1.2, CVCC1.2, CVCC2.2, D1.2 (A), D2.2 (A), D3.2 (A), D4.2 (A), D5.2 (A), D6.2 (A), D7.2 (A), D8.2 (A), D9.2 (A), D11.2 (A), J2.1, J4.2, J5.1, J6.1, J7.1, J8.1, J9.1, J10.1, J11.8, J12.2, J15.1 (Pin_1_1), J24.1, NT1.2, NT2.2, NT3.2, NT4.2, NT5.2, NT6.2, NT7.2, NT8.2, NT9.2, NT10.2, NT11.2, Q1.1 (S), Q3.3 (S), Q5.1 (S), Q6.1 (S), Q8.1 (S), Q9.1 (S), RBS2.2, RESTP3.2, RESTP4.1, RESTP6.2, RESTP8.2, RESTP9.1, RPD1.1, RPD2.1, RPDP1.2, RPDQ1.2, RPRE1.3 (GND_3), RPS2.2, TP1.1 (1_1), TP2.1 (1_1), TP3.1 (1_1), TP16.1 (1_1), TP20.1 (1_1), U2.10 (PGND), U2.25 (EP), U3.1 (PGND), U3.11 (PGND), U6.4 (GND), U6.5 (IN-), U7.10 (PGND), U7.25 (EP), U13.1 (GND), U13.4 (GND), U14.1 (GND), U14.4 (GND), U15.1 (GND), U15.4 (GND)

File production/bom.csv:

Designator,Footprint,Quantity,Value,LCSC Part #
"CBLK3, CBLK4, CBLK5, CBLK6, CBLK7, CBLK8",CP_Elec_18x22,6,470u,C3829592
"CBLKA1, CBLKA2, CBULK2, CIN1B2",CP_Elec_10x10,4,100uF,C5246576
"CBLKA3, CBLKA4, CIN1A1, CIN1B1",CP_Elec_10x10,4,47uF,C164068
"CBOOT1, CBOOT3, CCS1, CCS2, CCS3, CCS4, CCS5, CCS6, CCS7, CCS8, CCS9, CVDDA1, CVDDA2",0603,13,100n,C1591
"CBOOT2, CBS1, COUT3A1, COUT4B1, CPS1",0603,5,100nF,C1591
CCOMP1,0603,1,2nF,C1870141
CCOMP2,0603,1,2.7nF,C77034
CCS10,CP_Elec_6.3x5.4,1,100uF 35V,C5138965
"CCS11, CCS12",0603,2,100nF 50V,C1591
"CCSF1, CCSF2, CCSF4, CCSF5, CCSF6, CCSF7, CCSF8",0603,7,10n,C519406
"CDRV1, CVCCA1",0805,2,1uF,C24123
CEN1,0603,1,1nF,C1588
"CFF1, CHF1, CHF2",0603,3,22pF,C1653
"CHF4A1, CIN3A1",0805,2,220nF,C513710
CIN2A1,1210,1,4.7uF,C381466
"CIN2B1, CIN2B2, CIN3B1, CIN3B2, CIN4B1, CIN4B2, CINC1, CINC2, CINC3, CINC4, CINC5, CINC6, CINC7, CINC8",1210,14,4.7u,C381466
"CIN5A1, CIN5B1, CIN5B2, CINC10, CINC11, CINC12, CINC9, COUT4B2",0805,8,100nF,C344180
"COUT1A1, COUT2A1",1210,2,47uF,C77101
"COUT1B1, COUT1B2, COUT2B1, COUT2B2, COUT3B1, COUT3B2",1210,6,22uF,C778721
"CVCC1, CVCC2",0805,2,2.2u,C377773
"D1, D2, D4, D5, D6, D7",D_SMC,6,TVS,C438117
D11,D_SOD-123,1,3.3V Zener,C235771
D3,D_SMC,1,TVS,C438106
D8,D_SMC,1,TVS,C492903
D9,D_SMA,1,12V Zener 1W,C110523
DFB1,D_SMA,1,S1M,C155378
F1,FUSE_BF1_M5_100A,1,Fuse,
"F10, F8",1206,2,0.5A,
"F2, F3, F4, F5, F6, F7",LITTELFUSE_178.6165.0002,6,~,
"J10, J7, J8, J9",AMASS_XT30UPB-F_1x02_P5.0mm_Vertical,4,Conn_01x02,C108769
J11,JST_GH_BM08B-GHS-TBT_1x08-1MP_P1.25mm_Vertical,1,Conn_01x08,C133062
J12,"PhoenixContact_MC_1,5_2-G-3.81_1x02_P3.81mm_Horizontal",1,6V Out,C480537
J13,MountingHole_5.3mm_M5_Pad_Via_HP,1,PRECIN,
J14,MountingHole_5.3mm_M5_Pad_Via_HP,1,PRECOUT,
J15,MountingHole_5.3mm_M5_Pad_Via_HP,1,Conn_Batt_GND,
J16,MountingHole_5.3mm_M5_Pad_Via_HP,1,Dump_Resistor_In,
J17,MountingHole_5.3mm_M5_Pad_Via_HP,1,Dump_Resistor_Out,
J18,PinHeader_1x02_P2.54mm_Vertical,1,BC_Disconnect,C492401
J2,JST_GH_BM04B-GHS-TBT_1x04-1MP_P1.25mm_Vertical,1,Conn_01x04,C161692
J20,TerminalBlock_MaiXu_MX126-5.0-02P_1x02_P5.00mm,1,ESTOP Contactor Coil Control,C5188434
J21,TerminalBlock_MaiXu_MX126-5.0-02P_1x02_P5.00mm,1,ESTOP Button (Normally Closed),C5188434
J22,TerminalBlock_MaiXu_MX126-5.0-02P_1x02_P5.00mm,1,Precharge Contactor Coil Control,C5188434
J24,JST_GH_BM06B-GHS-TBT_1x06-1MP_P1.25mm_Vertical,1,Precharge Ctrl In,C189892
J3,MountingHole_5.3mm_M5_Pad_Via_HP,1,Conn_Batt_PWR,
J4,"PhoenixContact_MC_1,5_2-G-3.81_1x02_P3.81mm_Horizontal",1,3.3V Out,C480537
J5,"PhoenixContact_MC_1,5_2-G-3.81_1x02_P3.81mm_Horizontal",1,24V Out -> Jetson,C480537
J6,"PhoenixContact_MC_1,5_2-G-3.81_1x02_P3.81mm_Horizontal",1,24V Out -> USB-C-PD controller,C480537
JESTOP1,MountingHole_5.3mm_M5_Pad_Via_HP,1,ESTOP_IN,
JESTOP2,MountingHole_5.3mm_M5_Pad_Via_HP,1,ESTOP_OUT,
L1,L_Sumida_CDRH104R,1,18uH,C225049
L2,L_Coilcraft_XAL8080-XXX,1,10uH,C49261520
L3,L_Coilcraft_XAL8080-XXX,1,4.7uH,C7432408
"NT1, NT10, NT11, NT2, NT3, NT4, NT5, NT6, NT7, NT8, NT9",NetTie_AGND_PGND_VIA,11,NetTie_2,
"Q1, Q5, Q6, Q8, Q9",VSONP-8-1EP_5x6_P1.27mm,5,BSC070N10LS5ATMA1,C3278731
"Q2, Q3",TO-252-3_TabPin2,2,NMOS IRFR220N,C506577
"Q4, Q7",VSONP-8-1EP_5x6_P1.27mm,2,BSC146N10LS5,C534417
"RBS1, RENT1, RUV1, RUV2",0603,4,100k,C122538
"RBS2, RPS2",0603,2,3.9k,C473237
RCOMP1,0603,1,19.1k,C149926
RCOMP2,0603,1,12.1k,C705723
"RCON1, RCON2",0603,2,41.2k,C705776
"RCSF1, RCSF2, RCSF4, RCSF5, RCSF6, RCSF7, RCSF8",0603,7,1k,C14676
RDIV1,0603,1,1M,C326730
RDIV2,0603,1,24k,C217904
"RDM1, RDM2",0603,2,2.2R,C22939
RENB1,0603,1,43.2k,C861404
"RESTP1, RESTP2, RG1",0603,3,100R,C22775
"RESTP3, RESTP4",0603,2,2.2k,C4190
RESTP5,0805,1,100k,C96346
RESTP6,0603,1,7.5k,C23234
RESTP7,2512,1,4.7K 1W,C163339
"RESTP8, RESTP9, RPD1, RPD2, RPDP1, RPDQ1",0603,6,100k,C14675
"RFB1, RFB2",0603,2,4.7R,C23164
RFB1A1,0603,1,64.9k,C861510
RFB1A2,0603,1,291k,C861285
"RFB2B1, RFB2B2, RPU3",0603,3,10k,C95204
RFBC1,0805,1,1.65M,C218412
RPRE1,TO-263-2_Resistor,1,100,C26159126
RPS1,0603,1,100k, C122538
"RSEN1, RSEN2",2512,2,0.004R,C105388
"RSF1, RSF2",0603,2,47k,C218044
"TP1, TP10, TP11, TP12, TP13, TP14, TP15, TP16, TP2, TP3, TP4, TP5, TP6, TP7, TP8, TP9",TestPoint_Keystone_5015_Micro_Mini,16,Keystone 5015,C2906768
TP20,TestPoint_Keystone_5015_Micro_Mini,1,PGND probe pad,
U1,SOT95P280X145-6N,1,TLV3011AIDBVT,C2867795
"U10, U11, U12, U4, U5, U8, U9",XDCR_ACS758LCB-100U-PFF-T,7,ACS758LCB-100B-PFF-T,C82405
"U13, U14, U15",SOT-23-5_MC_MCH,3,MCP1402T-E/OT,C128573
"U2, U7",QFN50P550X350X100-25N,2,LM5148RGYR,C7470701
U3,RNX0012B,1,LMR36015ARNXR,C1850345
U6,SOT95P280X145-6N,1,UCC27511DBVR,C191027
ZV50K2220801NIR1,2220,1,Varistor,C53286339

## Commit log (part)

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2026-04-06 Added input cap at 48->24 comp buck
2026-04-10 Converted 24V actuator rails to 48V actuator rails
2026-04-10 V10 change
2026-04-11 Test V10
2026-04-11 Added Pre charge tag
2026-04-11 test
2026-04-11 LM5143 48-24V Buck Interleaved Buck Converter
    KiCad Files and relevant Texas Instruments Documentation
2026-04-12 File added for master
2026-04-12 Resized page
2026-04-18 Added regen protection
2026-04-18 Added updated 48 to 3.3v converter
2026-04-18 small clean up
2026-04-19 Added regen MOSFET drivers
2026-04-19 Added PMOS to precharge
2026-04-19 schematic labeling
2026-04-19 Changed main buck
2026-04-21 Started on high side fet driver for precharge
2026-04-21 48V -> 6V buck added
2026-04-21 Fixed 48V -> 6V buck power source
2026-04-23 restructured actuator rails
2026-04-23 48->6 power conection update
2026-04-24 Added precharge high side nmos controler
2026-04-24 Changed current sensors to 3.3V
2026-04-26 tvs diodes for overvoltage protection at the battery input
2026-04-26 added TVS diodes for overvoltage protection for each actuator rail output and also the 24v and 6v rail outputs
2026-04-26 tvs diodes update
2026-04-26 caps
2026-04-27 Changed 48->24 to 48->12
2026-04-28 Format change
2026-04-29 updated component values for 6v convert
2026-04-29 updated grounds for converters, need to double check grounds for current sense. Did not adjust grounds on actuators/precharge. Added pull up resistor on 6v PG output.
2026-04-29 changed ground for ext comp circuit
2026-04-29 added thermistors in lower left hand side, exact values, quantity,and need for more specific measurement will be determined during testing/tracing.
2026-04-29 Grounding and inductor and output caps on 12V buck
2026-04-29 Added compute buck cap
2026-04-29 Added input caps to 6V buck
2026-04-30 Thermistors edit
2026-04-30 misc
2026-05-31 TVS diode grounding changes
2026-06-01 input/output caps on 3.3V rail update
2026-06-01 Revisions for 3.3V buck + Added footprints
2026-06-02 Started updating 48->12 buck footprints (caps and res)
2026-06-02 Added input cap to 48->12 buck
2026-06-02 Changed sf and ripple current %
2026-06-02 Added footprints for ics in 12V buck
2026-06-05 48->6V buck updates
2026-06-05 output caps on 6V rail
2026-06-05 test; no changes
2026-06-05 FET footprints added
2026-06-05 Added fuse holder footprints
2026-06-05 Setup main pour topology
2026-06-05 Added star point
2026-06-07 added footprints onto the PCB
2026-06-14 input caps on actuator rails updated with footprints
2026-06-14 Fixing Kicad crash
2026-06-14 Bulk caps and low pass filting on CS output
2026-06-14 back current updates + footprints
2026-06-15 Changed prechage to relay based system and added footprints to PCB
2026-06-16 added estop coil control circuit
2026-06-24 Added nets to all high current connections
2026-06-24 PCB for bulk caps and main curr sen
2026-06-25 PCB buck caps and 3.3V buck
2026-06-25 Adj vias in 3.3V buck
2026-06-25 redid 3.3 buck layout on pcb
2026-06-25 edited pgnd (upper) on 3.3V buck
2026-06-25 added additonal vias in pgnd pour
2026-06-26 bulk caps relayout and added power pours on bottom layer
2026-06-26 silkscreen updates
2026-06-27 fixed grounding error
2026-06-28 Revise README to include detailed project information
    Expanded the README to provide detailed information about the Humanoid Robot Power Distribution Board, including project overview, system architecture, power rails, major features, and design status.
2026-06-30 adj decoupling caps placements
